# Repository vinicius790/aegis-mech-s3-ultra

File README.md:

# AEGIS-MECH S3 (`v3.0 Ultra`) — Plataforma Mecatrônica, Eletrônica & IA Embarcada

Sistema ciberfísico autônomo em **ESP32-S3-WROOM-1-N16R8** (`Dual LX7 240 MHz`, `16 MB QIO Flash + 8 MB OPI PSRAM`), sensoriamento bayesiano redundante (`2× HC-SR04 RMT Ping-Pong + 2× VL53L1X + DS18B20 Magnus-Tetens + MPU6050 3-eixos + AS5600 + INA219 Kelvin + ATS ADC + E-Stop NF`), controle híbrido discreto estável (`SCurve` quíntico + Medição-D sem *derivative kick* + `ActuatorNet` + verificador `Faddeev-LeVerrier`), TinyML bit-exact (`Tiny1DCNNBio` 4.879 params folded + OOD + TamperNet), Visão 2FA OpenCV real (`ArUco + HSV + DangerDetector IoU + MediaPipe/DogTracker`), Digital Twin vetorizado estilo NVIDIA Isaac Lab (`aegis_sim/`) e Cockpit SCADA Live SSE.

Consulte o plano mestre completo em [Plano de desenvolvimento.md](../Plano%20de%20desenvolvimento.md).

## Estrutura Principal
- `hardware/` — `BOM v3.0`, limites, pinout `41 pinos`, chicote `harness_wireviz.yml`, projeto `KiCad 8` 4 camadas e netlist auditável.
- `cad/` — `7` modelos `OpenSCAD v3.0` imprimíveis (`painel_sensores` `56 mm`, `arena_base` com cones `VL53L1X`, `trava_cremalheira` `m=1.25 Z=16 AS5600`, `caixa_cofre` c/ furo E-Stop Ø22 e `3× mounts`).
- `firmware/` — FreeRTOS Dual-Core (`espressif32@^6.9.0` IDF 4.4 `<driver/rmt.h>` + `qio_opi`), partições `16 MB`, POST real `20/20`, `AEGIS-PROTO v1` (`0x01..0x08`) e `tools/bringup/01..04`.
- `python/aegis_ai/` — IA Bit-Exact, `aegis_sim/` vetorizado, `control_stability.py` (`Faddeev-LeVerrier` + `Durand-Kerner`), `psychrometry.py` (`Magnus-Tetens`) e `vision_2fa/` completo OpenCV.
- `demo/` — `app_web.py` (SSE 30 Hz + 5 painéis), `circuit_netlist_auditor.py`, `diagnostic_agent.py` (ROSA Read-Only + AST Guard), `rerun_logger.py`, `lerobot_arm_bridge.py` e `serial_recorder.py`.
- `docs/` — **12 Laboratórios Executáveis (`lab_01..12.md`)**, especificação `protocolo_comunicacao.md`, integração real dos **20 ZIPs**, `wokwi/diagram.json`, `web_flasher/` (`boot_app0.bin @ 0xe000`) e [simuladores_3d_web.md](docs/simuladores_3d_web.md).

## Comandos Rápidos
```powershell
py -m pytest -v
py demo/circuit_netlist_auditor.py --netlist hardware/kicad/aegis_mech_s3_netlist.json --strict
py demo/circuit_netlist_auditor.py --netlist docs/wokwi/diagram.json --strict
py demo/diagnostic_agent.py
py demo/app_web.py
```

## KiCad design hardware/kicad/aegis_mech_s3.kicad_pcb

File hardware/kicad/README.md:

# Projeto Eletrônico KiCad 8.0 — AEGIS-MECH S3

- **Esquemático:** `aegis_mech_s3.kicad_sch`
- **Layout PCB:** `aegis_mech_s3.kicad_pcb` (4 Camadas: F.Cu, In1.Cu GND, In2.Cu Power, B.Cu)
- **Regras DFM:** JLCPCB 4-Layer Standard (trilhas mínimas 0,2 mm sinal, 2,5 mm potência, furos via 0,3 mm).
- **Testpoints Mapeados:** TP1 (+12V Fused), TP2 (+5V Bus), TP3 (+3V3 Dig), TP4 (GND Star), TP5/TP6 (I2C SDA/SCL), TP7 (ECHO 3,23V), TP8 (Shunt INA219).

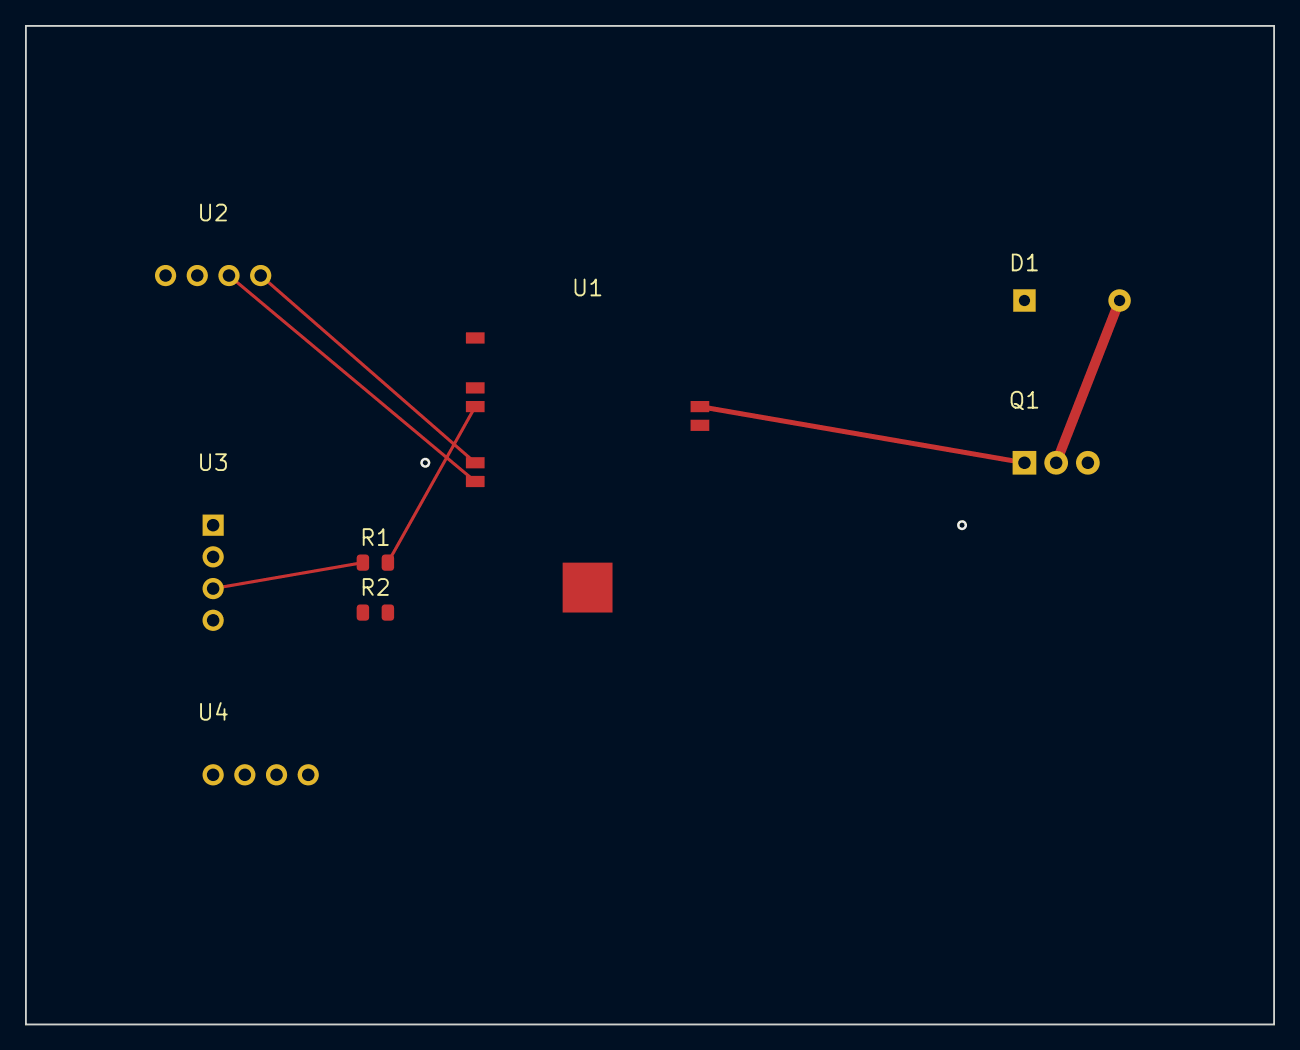
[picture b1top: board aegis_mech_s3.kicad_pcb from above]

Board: 2 copper layers, 100.0 x 80.0 mm, 8 parts (0 on the bottom side), 9 nets.

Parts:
D1: 1N5819; D_DO-41_SOD81_P7.62mm_Horizontal
Q1: IRLZ44N; TO-220-3_Vertical
R1: 1.2k; R_0805_2012Metric
R2: 2.2k; R_0805_2012Metric
U1: ESP32-S3-WROOM-1-N16R8; ESP32-S3-WROOM-1
U2: VL53L1X; VL53L1X_Breakout
U3: HC-SR04; PinHeader_1x04_P2.54mm_Vertical
U4: MPU6050; MPU-6050_Breakout

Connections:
+3V3: U1.1, U2.1, U4.1
+5V_BUCK: D1.1, U3.1
ECHO_3V3: R1.2, R2.1, U1.5
ECHO_5V: R1.1, U3.3
GND: Q1.3, R2.2, U1.40, U2.2, U3.4, U4.2
I2C_SCL: U1.9, U2.3, U4.3
I2C_SDA: U1.8, U2.4, U4.4
NET_DRAIN: D1.2, Q1.2
TRIG_OUT: U1.4, U3.2
